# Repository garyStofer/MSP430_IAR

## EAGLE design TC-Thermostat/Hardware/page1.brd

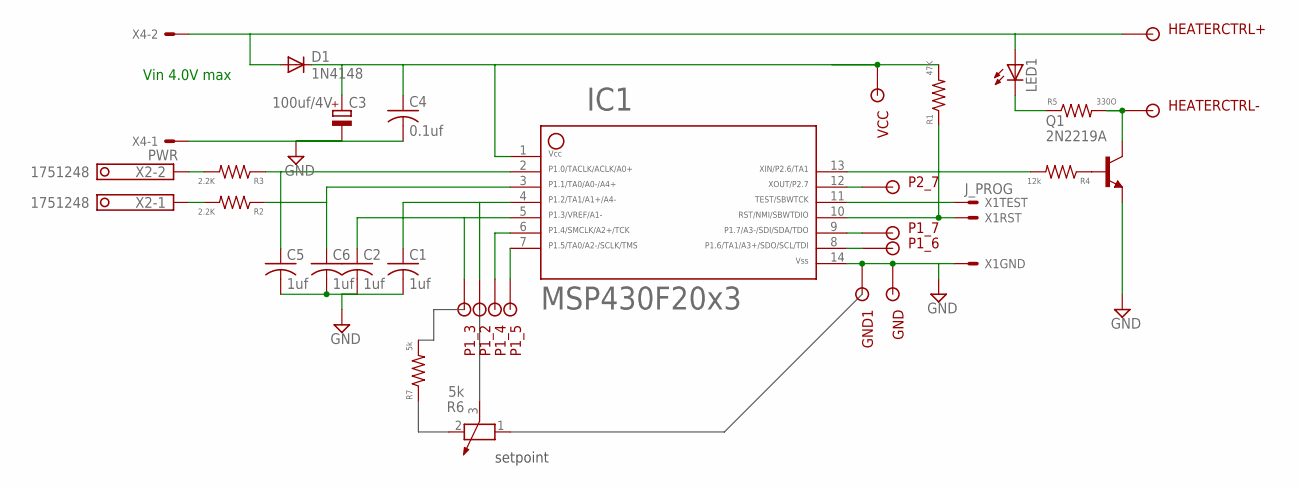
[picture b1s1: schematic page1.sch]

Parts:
C1, C2, C5, C6: 1uf; C0805
C3: 100uf/4V; SMC_B
C4: 0.1uf; C0805
D1: 1N4148; DIO-35-10
GND, GND1: SOLDER_POINTA; P1-13
HEATERCTRL+: SOLDER_POINTA; P1-13
HEATERCTRL-: SOLDER_POINTA; P1-13
IC1: F20X3---N14; N14
LED1: LED5MM
P1_2, P1_3, P1_4, P1_5, P1_6, P1_7, P2_7: SOLDER_POINTA; P1-13
Q1: 2N2219A; TO92-EBC
R1: 47K; M0805
R2, R3: 2.2K; M0805
R4: 12k; M0805
R5: 330O; 0207/15
R6: 5k; PT-10
R7: 5k; 0207/15
VCC: SOLDER_POINTA; P1-13
X1: J_PROG; MOLEX-3PIN
X2: 1751248
X4: PWR; 22-23-2021

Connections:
GND: C1.2, C2.2, C3.-, C4.2, C5.2, C6.2, GND.1, GND1.1, IC1.14, Q1.E, X1.3, X4.1
unnamed: IC1.10, R1.1, X1.2
unnamed: IC1.11, X1.1
unnamed: C3.+, C4.1, D1.P$1 (C), IC1.1, R1.2, VCC.1
unnamed: R2.2, X2.1
unnamed: R3.2, X2.2
unnamed: Q1.B, R4.1
unnamed: C2.1, IC1.5, P1_3.1
unnamed: D1.P$2 (A), HEATERCTRL+.1, LED1.A, X4.2
unnamed: C1.1, IC1.4, P1_2.1
unnamed: IC1.13, R4.2
unnamed: HEATERCTRL-.1, Q1.C, R5.2
unnamed: LED1.K (C), R5.1
unnamed: IC1.6, P1_4.1
unnamed: IC1.7, P1_5.1
unnamed: C5.1, IC1.2, R3.1
unnamed: C6.1, IC1.3, R2.1
unnamed: IC1.12, P2_7.1
unnamed: IC1.9, P1_7.1
unnamed: IC1.8, P1_6.1

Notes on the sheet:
Vin 4.0V max
setpoint

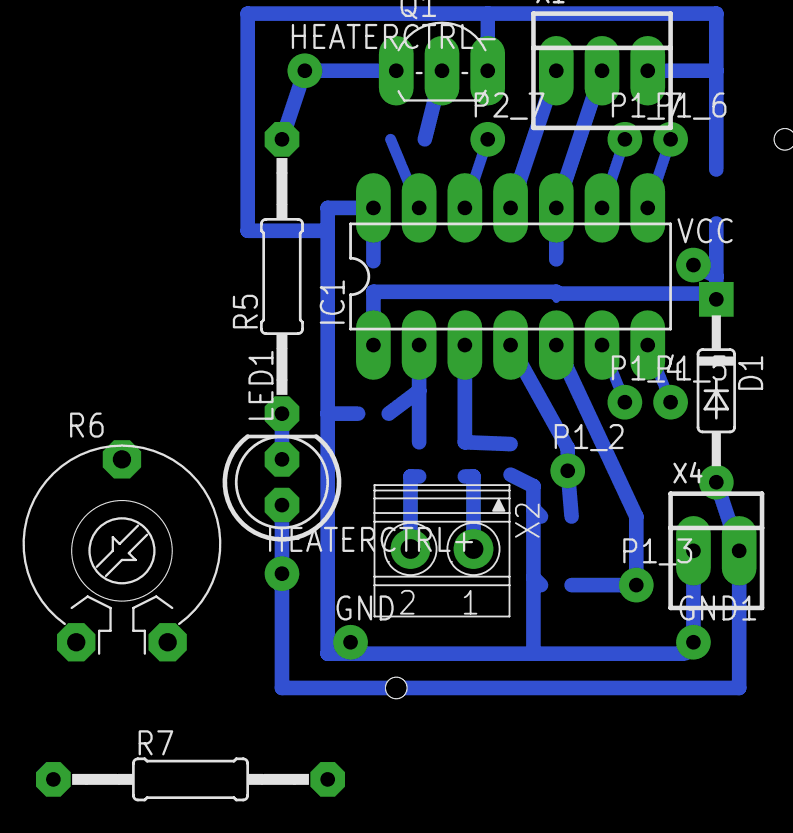
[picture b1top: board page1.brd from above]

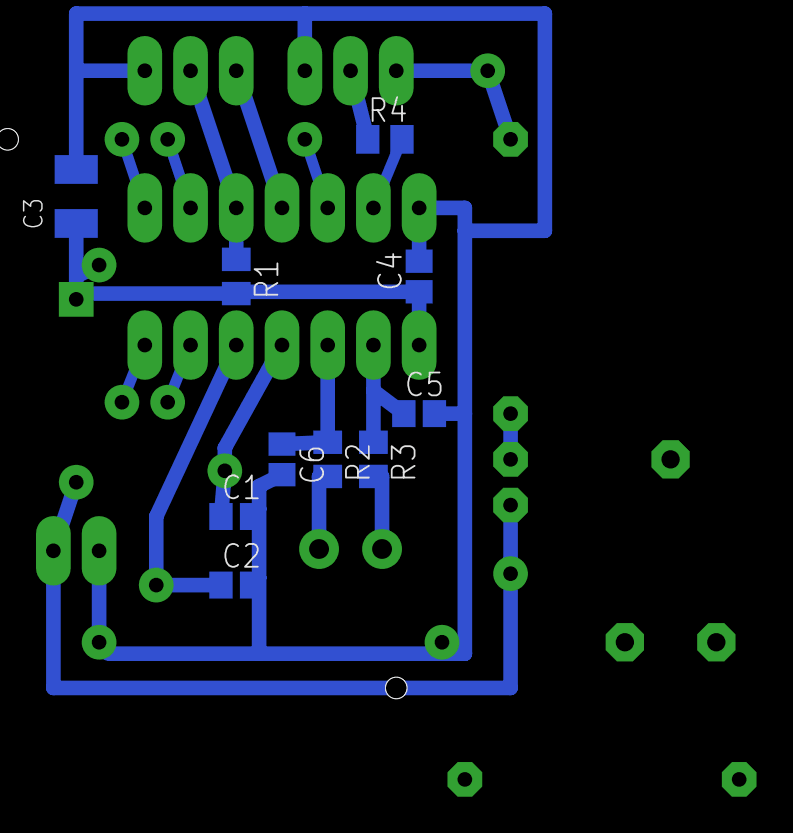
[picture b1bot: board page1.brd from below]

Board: 2 copper layers, 32 parts (10 on the bottom side), 20 nets.

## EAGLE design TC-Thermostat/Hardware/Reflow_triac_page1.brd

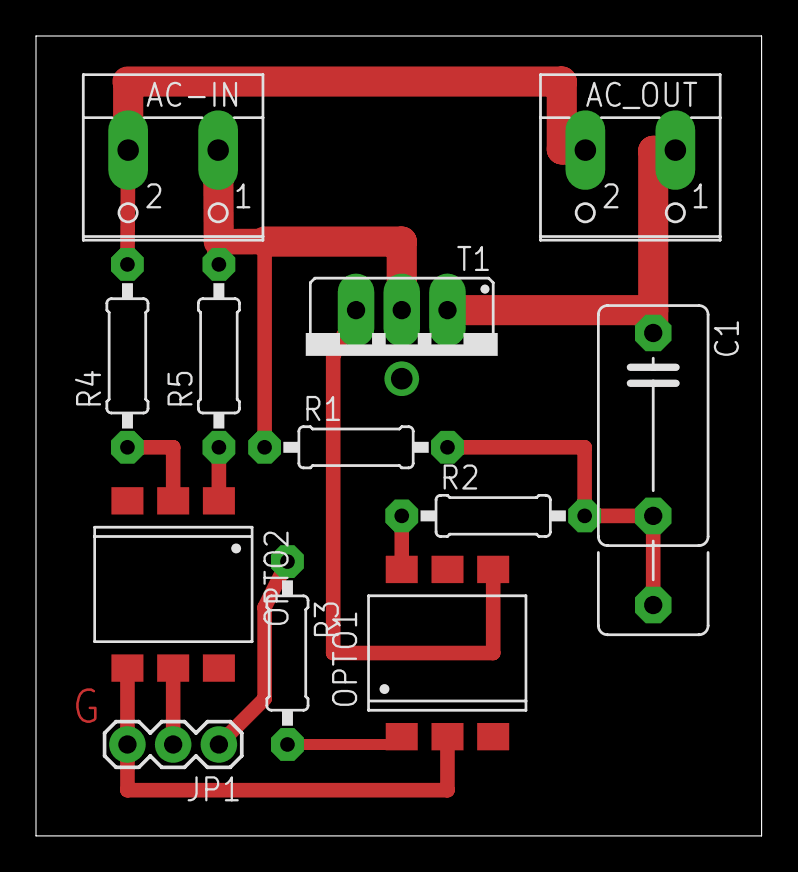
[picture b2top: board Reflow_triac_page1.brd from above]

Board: 2 copper layers, 40.3 x 44.4 mm, 12 parts (0 on the bottom side), 12 nets.

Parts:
AC-IN: W237-102
AC_OUT: W237-102
C1: 0.1uf/1000; C102_152-062X184
JP1: 1X03
OPTO1: MOC3020S; DIL6-SMD
OPTO2: H11AA1SR2M; DIL6-SMD
R1: 2.4K; 0207/10
R2: 180; 0207/10
R3: 330; 0207/10
R4, R5: 40k; 0207/10
T1: BT137XVERTICAL; TO220DS

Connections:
GND: JP1.3, OPTO1.2, OPTO2.4
unnamed: AC-IN.1, R1.1, R5.2, T1.A2
unnamed: AC_OUT.1, C1.1, T1.A1
unnamed: OPTO1.4, T1.G
unnamed: C1.2, R1.2, R2.2
unnamed: OPTO1.6, R2.1
unnamed: OPTO1.1, R3.2
unnamed: OPTO2.2, R4.1
unnamed: AC-IN.2, AC_OUT.2, R4.2
unnamed: OPTO2.1, R5.1
TRIAC_CTRL: JP1.1, R3.1
ZERO_XING: JP1.2, OPTO2.5

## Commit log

2012-03-30 Creating_initial_branch_structure
2012-03-30 deleted unneeded files
2012-03-30 unversioned tutor
2024-05-17 Added code and schematic for setpoint. fixed polynomial to calculate TC temperature to use all 9 degrees. added the Eagle hardware files for the MSP430 controller and the Triac circuit. added relevan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
2024-05-17 added revised PCB schematic for TC_thermostat

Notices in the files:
parts and their libraries:
SparkFun-Connectors: Licensing: CC v3.0 Share-Alike You are welcome to use this library for commercial purposes.
